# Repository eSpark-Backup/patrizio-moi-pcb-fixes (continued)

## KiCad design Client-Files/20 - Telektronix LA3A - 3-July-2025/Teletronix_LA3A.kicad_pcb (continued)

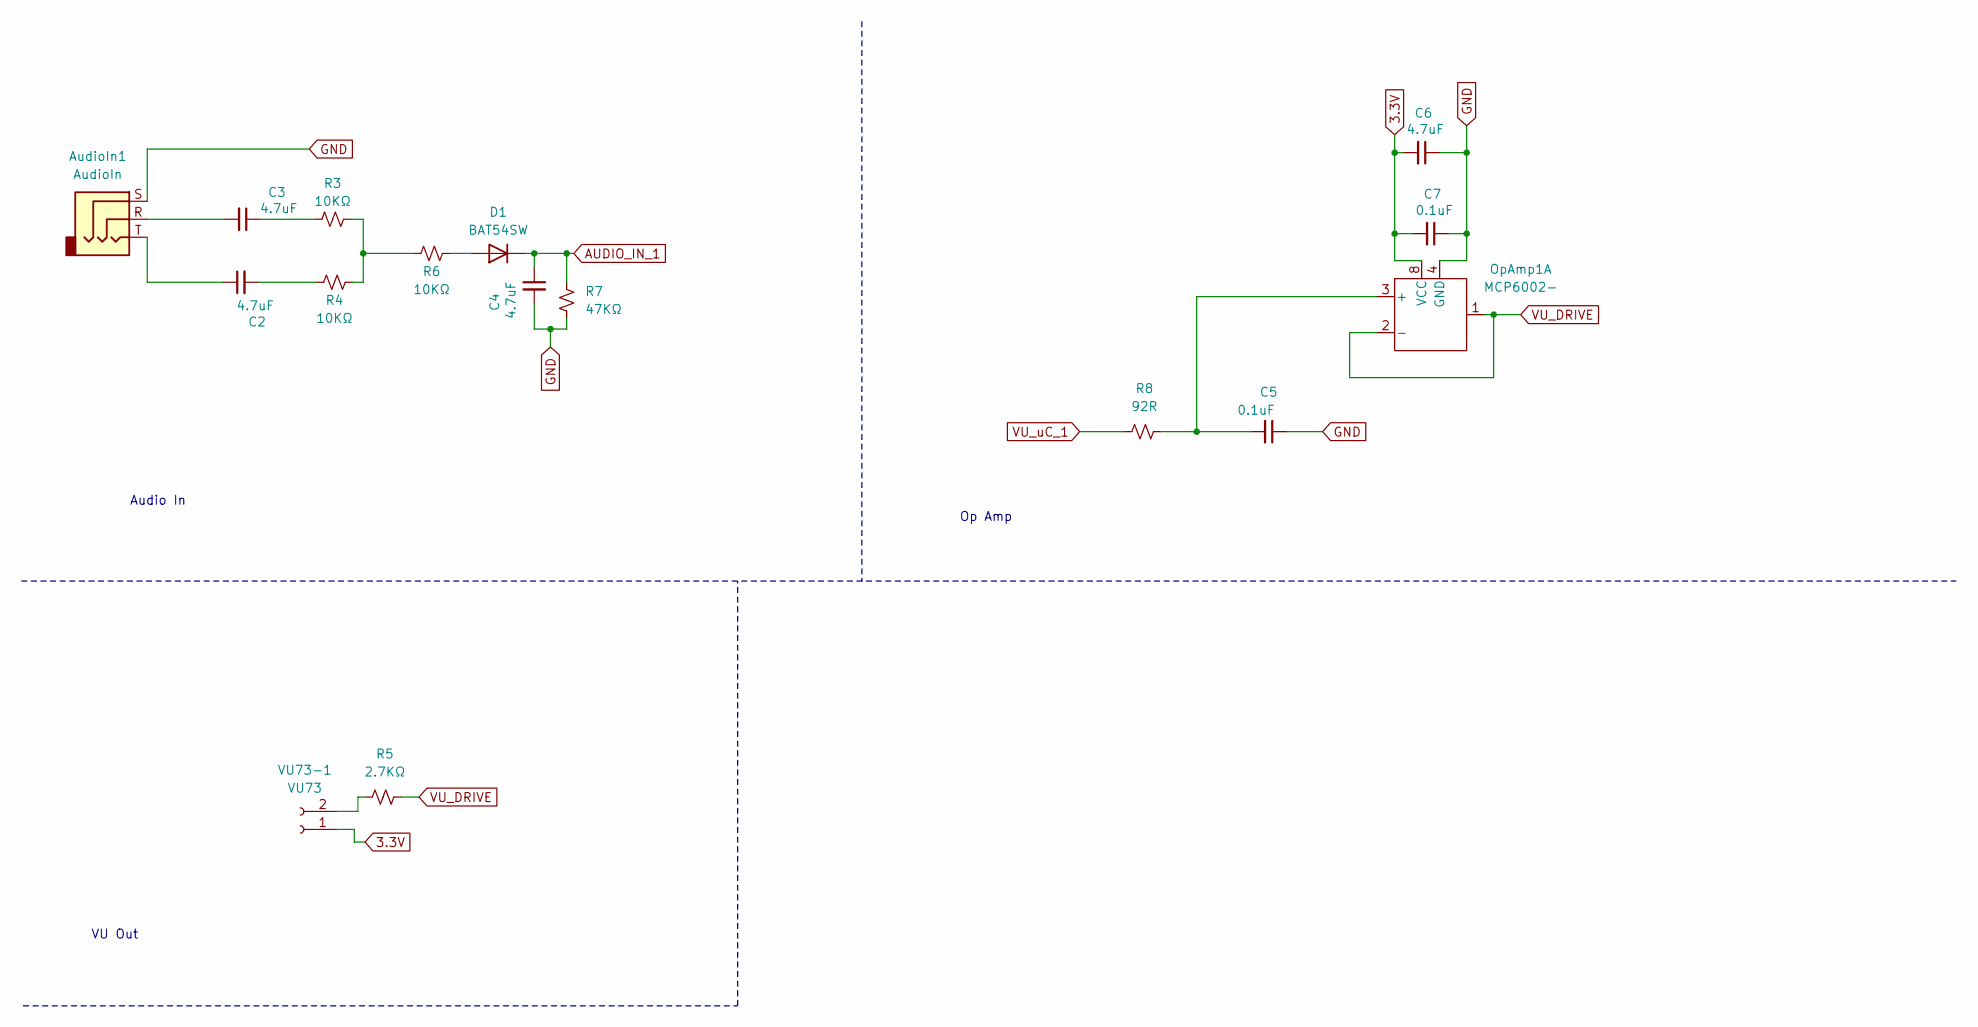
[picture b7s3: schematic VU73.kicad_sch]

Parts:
AudioIn1: AudioIn; Jack_3.5mm_PJ320D_Horizontal; LCSC Part Number C22459515
C2, C3, C4, C6: 4.7uF; C_0402_1005Metric; LCSC Part Number C23733
C5: 0.1uF; C_0402_1005Metric
C7: 0.1uF; C_0402_1005Metric; LCSC Part Number C1525
D1: BAT54SW; D_SOD-323; LCSC Part Number C27636114
OpAmp1: MCP6002-; SOIC-8_3.9x4.9mm_P1.27mm; LCSC Part Number C7377
R3, R4, R6: 10KΩ; R_0402_1005Metric; LCSC Part Number C25744
R5: 2.7KΩ; R_0603_1608Metric; LCSC Part Number C13167
R7: 47KΩ; R_0402_1005Metric; LCSC Part Number C25792
R8: 92R; R_0402_1005Metric
VU73-1: VU73; PinSocket_1x02_P2.54mm_Vertical

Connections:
3.3V: C6.2, C7.2, OpAmp1.8 (VCC), VU73-1.1; also elsewhere on the board
AUDIO_IN_1: C4.1, D1.1 (K), R7.2; also elsewhere on the board
GND: AudioIn1.S, C4.2, C5.1, C6.1, C7.1, OpAmp1.4 (GND), R7.1; also elsewhere on the board
unnamed: AudioIn1.R, C3.2
unnamed: AudioIn1.T, C2.1
unnamed: C2.2, R4.2
unnamed: C3.1, R3.2
unnamed: D1.2 (A), R6.1
unnamed: C5.2, OpAmp1.3 (+), R8.1
unnamed: R3.1, R4.1, R6.2
unnamed: R5.2, VU73-1.2
VU_DRIVE: OpAmp1.1, OpAmp1.2 (-), R5.1
VU_uC_1: R8.2; also elsewhere on the board

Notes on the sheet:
VU Out
Op Amp
Audio In

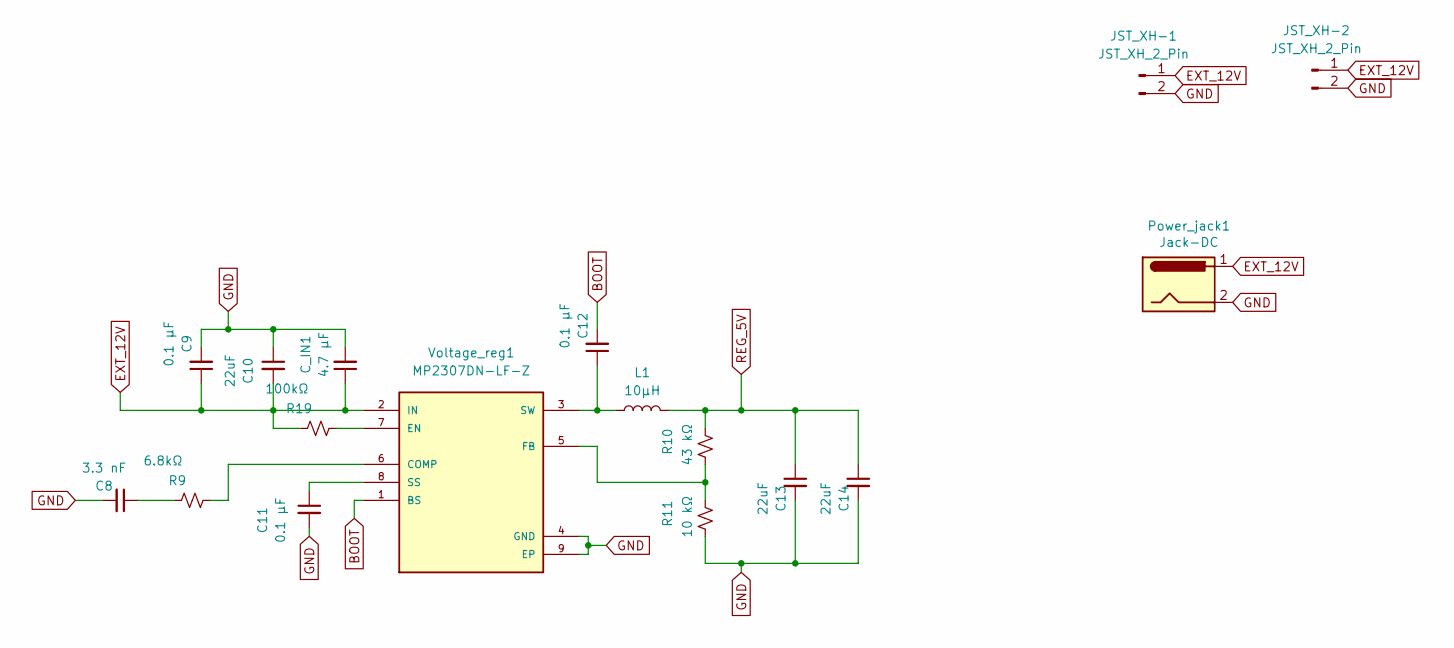
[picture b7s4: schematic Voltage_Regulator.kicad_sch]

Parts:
C8: 3.3 nF; C_0603_1608Metric; LCSC Part Number C1613
C9, C11, C12: 0.1 µF; C_0402_1005Metric; LCSC Part Number C1525
C10, C13, C14: 22uF; C_0603_1608Metric; LCSC Part Number C59461
C_IN1: 4.7 µF; C_0402_1005Metric; LCSC Part Number C23733
JST_XH-1, JST_XH-2: JST_XH_2_Pin; JST_XH_B2B-XH-A_1x02_P2.50mm_Vertical
L1: 10µH; L_Bourns-SRN8040_8x8.15mm; LCSC Part Number C37429
Power_jack1: Jack-DC; BarrelJack_Horizontal
R9: 6.8kΩ; R_0603_1608Metric; LCSC Part Number C23212
R10: 43 kΩ; R_0402_1005Metric; LCSC Part Number C2906943
R11: 10 kΩ; R_0402_1005Metric; LCSC Part Number C25744
R19: 100kΩ; R_0603_1608Metric
Voltage_reg1: MP2307DN-LF-Z; SOIC-8-1EP_3.9x4.9mm_P1.27mm_EP2.29x3mm_ThermalVias; PARTREV 1.9; LCSC Part Number C2928813

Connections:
BOOT: C12.2, Voltage_reg1.1 (BS)
EXT_12V: C9.1, C10.2, C_IN1.1, JST_XH-1.1, JST_XH-2.1, Power_jack1.1, R19.1, Voltage_reg1.2 (IN)
GND: C8.2, C9.2, C10.1, C11.2, C13.2, C14.2, C_IN1.2, JST_XH-1.2, JST_XH-2.2, Power_jack1.2, R11.2, Voltage_reg1.4 (GND), Voltage_reg1.9 (EP); also elsewhere on the board
unnamed: C8.1, R9.1
unnamed: R9.2, Voltage_reg1.6 (COMP)
unnamed: R19.2, Voltage_reg1.7 (EN)
unnamed: R10.2, R11.1, Voltage_reg1.5 (FB)
unnamed: C11.1, Voltage_reg1.8 (SS)
unnamed: C12.1, L1.1, Voltage_reg1.3 (SW)
REG_5V: C13.1, C14.1, L1.2, R10.1; also elsewhere on the board

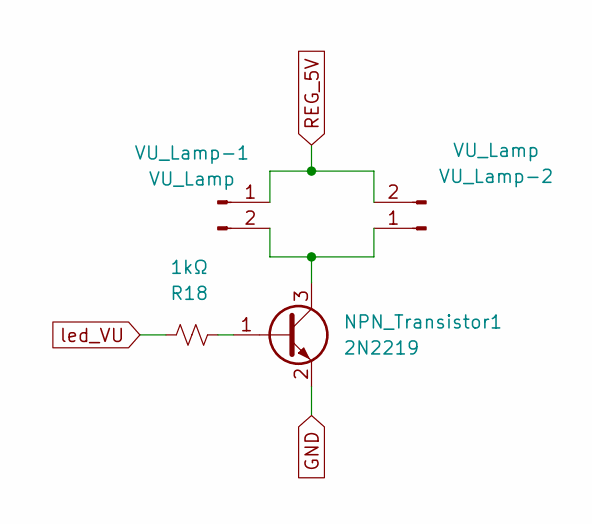
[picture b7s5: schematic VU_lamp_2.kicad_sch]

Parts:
NPN_Transistor1: 2N2219; SOT-23; LCSC Part Number C2150
R18: 1kΩ; R_0402_1005Metric; Manufacturer_Part_Number 0402WGF3300TCE; LCSC Part Number C11702
VU_Lamp-1, VU_Lamp-2: VU_Lamp; PinSocket_1x02_P2.54mm_Vertical

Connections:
GND: NPN_Transistor1.2 (E); also elsewhere on the board
unnamed: NPN_Transistor1.1 (B), R18.1
unnamed: NPN_Transistor1.3 (C), VU_Lamp-1.2, VU_Lamp-2.1
REG_5V: VU_Lamp-1.1, VU_Lamp-2.2; also elsewhere on the board
led_VU: R18.2; also elsewhere on the board

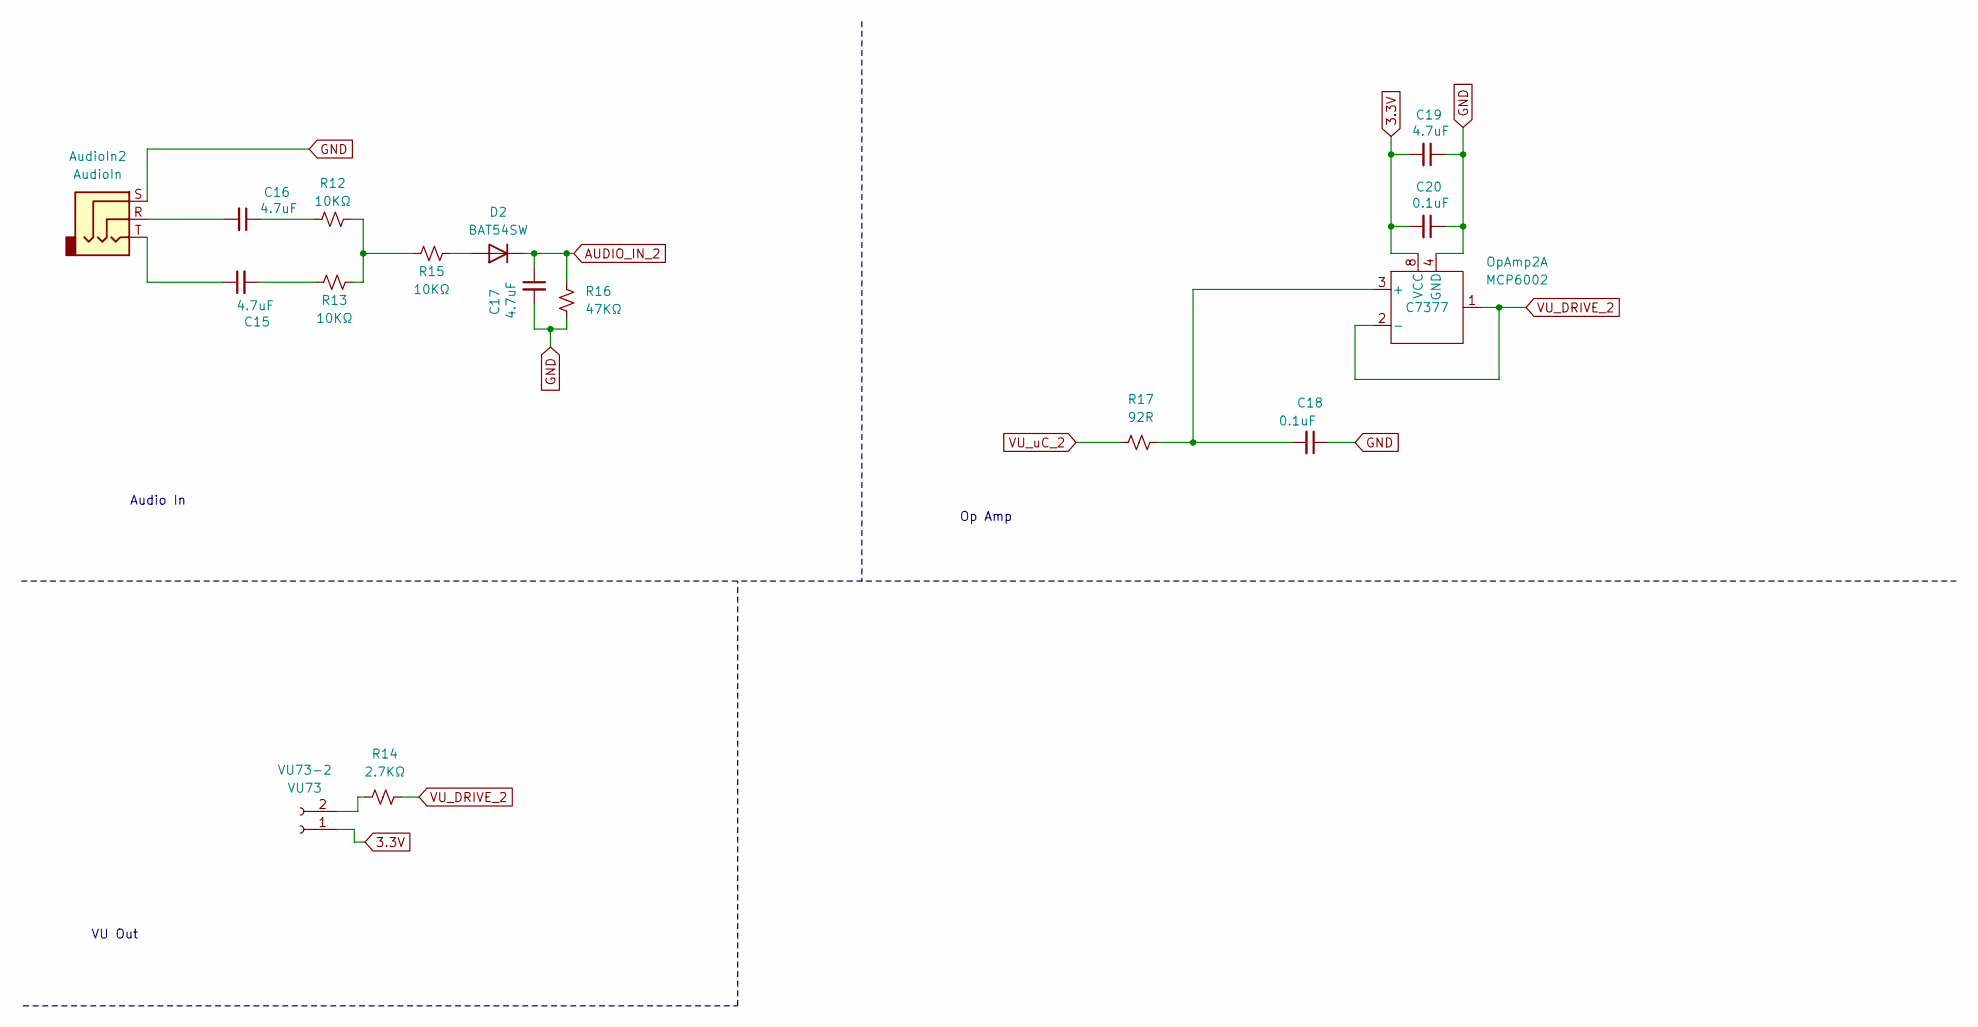
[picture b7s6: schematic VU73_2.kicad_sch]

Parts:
AudioIn2: AudioIn; Jack_3.5mm_PJ320D_Horizontal
C15, C16, C17, C19: 4.7uF; C_0402_1005Metric; LCSC Part Number C23733
C18: 0.1uF; C_0402_1005Metric
C20: 0.1uF; C_0402_1005Metric; LCSC Part Number C1525
D2: BAT54SW; D_SOD-323; LCSC Part Number C27636114
OpAmp2: MCP6002; SOIC-8_3.9x4.9mm_P1.27mm; LCSC Part Number C7377
R12, R13, R15: 10KΩ; R_0402_1005Metric; LCSC Part Number C25744
R14: 2.7KΩ; R_0603_1608Metric; LCSC Part Number C13167
R16: 47KΩ; R_0402_1005Metric; LCSC Part Number C25792
R17: 92R; R_0402_1005Metric
VU73-2: VU73; PinSocket_1x02_P2.54mm_Vertical

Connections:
3.3V: C19.2, C20.2, OpAmp2.8 (VCC), VU73-2.1; also elsewhere on the board
AUDIO_IN_2: C17.1, D2.1 (K), R16.2; also elsewhere on the board
GND: AudioIn2.S, C17.2, C18.1, C19.1, C20.1, OpAmp2.4 (GND), R16.1; also elsewhere on the board
unnamed: AudioIn2.R, C16.2
unnamed: AudioIn2.T, C15.1
unnamed: C15.2, R13.2
unnamed: C16.1, R12.2
unnamed: D2.2 (A), R15.1
unnamed: C18.2, OpAmp2.3 (+), R17.1
unnamed: R12.1, R13.1, R15.2
unnamed: R14.2, VU73-2.2
VU_DRIVE_2: OpAmp2.1, OpAmp2.2 (-), R14.1
VU_uC_2: R17.2; also elsewhere on the board

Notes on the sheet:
VU Out
Op Amp
Audio In

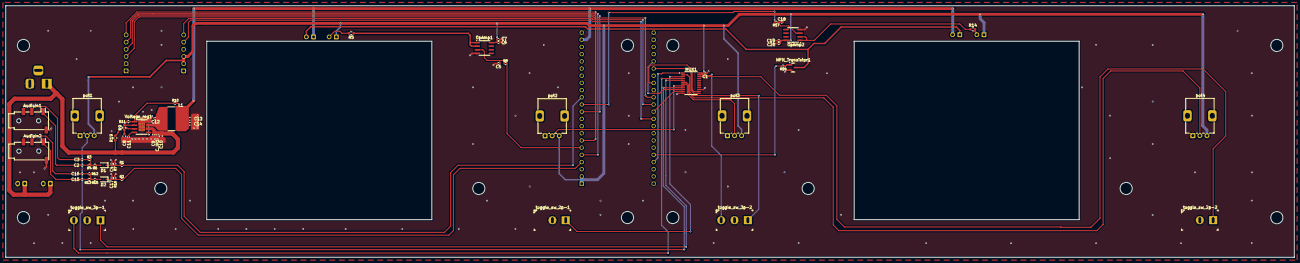
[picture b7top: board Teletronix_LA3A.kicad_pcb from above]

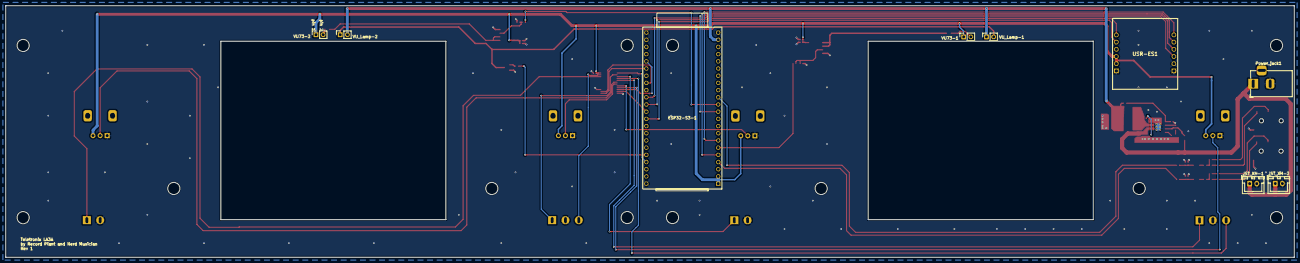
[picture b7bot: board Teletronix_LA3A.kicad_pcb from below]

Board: 2 copper layers, 455.0 x 88.8 mm, 67 parts (9 on the bottom side), 59 nets.

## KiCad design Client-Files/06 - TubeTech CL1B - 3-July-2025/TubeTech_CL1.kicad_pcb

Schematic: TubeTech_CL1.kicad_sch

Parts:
ESP32-S3-1: ESP32-S3-DevKitC; ESP32-S3-DEVKITC-1-N8R2-2
R1: 4.7KΩ; R_0402_1005Metric; LCSC Part Number C25900
USR-ES1: USR-ES1; USRES1; Manufacturer_Part_Number USR-ES1

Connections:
3.3V: ESP32-S3-1.1 (3V3), ESP32-S3-1.2 (3V3), USR-ES1.B2 (3V3_1), USR-ES1.B3 (3V3_2); also elsewhere on the board
AUDIO_IN: R1.1; also elsewhere on the board
CS: ESP32-S3-1.5 (GPIO5/ADC1_CH4), USR-ES1.A5 (CS)
GND: ESP32-S3-1.22 (GND), ESP32-S3-1.23 (GND), ESP32-S3-1.24 (GND), ESP32-S3-1.44 (GND), USR-ES1.A1 (GND_1), USR-ES1.A2 (GND_2), USR-ES1.B1 (GND_3); also elsewhere on the board
INT: ESP32-S3-1.7 (GPIO7/ADC1_CH6), USR-ES1.A6 (INT)
MISO: ESP32-S3-1.33 (GPIO36), USR-ES1.B6 (MISO)
MOSI: ESP32-S3-1.32 (GPIO35), USR-ES1.A3 (MOSI)
unnamed: ESP32-S3-1.13 (GPIO3/ADC1_CH2), R1.2
PWR_BTN: ESP32-S3-1.10 (GPIO17/ADC2_CH6); also elsewhere on the board
PWR_LED: ESP32-S3-1.29 (GPIO48); also elsewhere on the board
REG_5V: ESP32-S3-1.21 (5V); also elsewhere on the board
RST: ESP32-S3-1.35 (GPIO38), USR-ES1.B5 (RST)
S0: ESP32-S3-1.27 (GPIO21); also elsewhere on the board
S1: ESP32-S3-1.34 (GPIO37); also elsewhere on the board
S2: ESP32-S3-1.30 (GPIO45); also elsewhere on the board
S3: ESP32-S3-1.28 (GPIO47); also elsewhere on the board
SCLK: ESP32-S3-1.11 (GPIO18/ADC2_CH7), USR-ES1.A4 (SCLK)
VU_uC_1: ESP32-S3-1.6 (GPIO6/ADC1_CH5); also elsewhere on the board
led_VU: ESP32-S3-1.4 (GPIO4/ADC1_CH3); also elsewhere on the board
sig_1: ESP32-S3-1.41 (GPIO1/ADC1_CH0); also elsewhere on the board

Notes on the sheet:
Ethernet Module
ESP32-S3

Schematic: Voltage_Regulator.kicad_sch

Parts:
C10: 3.3 nF; C_0603_1608Metric; LCSC Part Number C1613
C11, C13, C14: 0.1 µF; C_0402_1005Metric; LCSC Part Number C1525
C12, C15, C16: 22uF; C_0603_1608Metric; LCSC Part Number C59461
C_IN1: 4.7 µF; C_0402_1005Metric; LCSC Part Number C23733
JST_XH-1, JST_XH-2: JST_XH_2_Pin; JST_XH_B2B-XH-A_1x02_P2.50mm_Vertical
L1: 10µH; L_Bourns-SRN8040_8x8.15mm; LCSC Part Number C37429
Power_jack1: Jack-DC; BarrelJack_Horizontal
R14: 6.8kΩ; R_0603_1608Metric; LCSC Part Number C23212
R15: 43 kΩ; R_0402_1005Metric; LCSC Part Number C2906943
R16: 10 kΩ; R_0402_1005Metric; LCSC Part Number C25744
R18: 100kΩ; R_0603_1608Metric
Voltage_reg1: MP2307DN-LF-Z; SOIC-8-1EP_3.9x4.9mm_P1.27mm_EP2.29x3mm_ThermalVias; PARTREV 1.9; LCSC Part Number C2928813

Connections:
BOOT: C14.2, Voltage_reg1.1 (BS)
EXT_12V: C11.1, C12.2, C_IN1.1, JST_XH-1.1, JST_XH-2.1, Power_jack1.1, R18.1, Voltage_reg1.2 (IN)
GND: C10.2, C11.2, C12.1, C13.2, C15.2, C16.2, C_IN1.2, JST_XH-1.2, JST_XH-2.2, Power_jack1.2, R16.2, Voltage_reg1.4 (GND), Voltage_reg1.9 (EP); also elsewhere on the board
unnamed: C10.1, R14.1
unnamed: R14.2, Voltage_reg1.6 (COMP)
unnamed: R18.2, Voltage_reg1.7 (EN)
unnamed: R15.2, R16.1, Voltage_reg1.5 (FB)
unnamed: C13.1, Voltage_reg1.8 (SS)
unnamed: C14.1, L1.1, Voltage_reg1.3 (SW)
REG_5V: C15.1, C16.1, L1.2, R15.1; also elsewhere on the board

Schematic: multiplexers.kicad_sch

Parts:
C7: 0.1uF; C_0402_1005Metric; LCSC Part Number C1525
C8, C9: 2.2uF; C_0402_1005Metric; LCSC Part Number C12530
C17: 2.2uF; C_0402_1005Metric; Manufacturer_Part_Number CL05A225MQ5NSNC; LCSC Part Number C12530
MUX1: CD4067BMT/TR; TSSOP-24_4.4x7.8mm_P0.65mm; LCSC Part Number C7432333
R8, R11: 100Ω; R_0402_1005Metric; LCSC Part Number C25076
R9, R10, R12, R13: 2.2KΩ; R_0402_1005Metric; LCSC Part Number C25879
R19: 100Ω; R_0402_1005Metric; Manufacturer_Part_Number 0402WGF1000TCE; LCSC Part Number C25076
R20: 2.2KΩ; R_0402_1005Metric; Manufacturer_Part_Number 0402WGF2201TCE; LCSC Part Number C25879
RTRY_SW1: SW_Rotary_1x2; SW_Rotary_RS25-2P
SW1, SW2: SW_Rotary_1x3_MP; SW_Rotary_RS25-3P
pot1, pot2, pot3, pot4, pot5, pot6: b10k; Potentiometer_Alps_RK09K_Single_Vertical
tgl_sw_3p-1: SW_SPDT; Toggle_Switch-3-pins

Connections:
3.3V: C7.2, MUX1.24 (VCC), R10.1, R13.1, R20.1, RTRY_SW1.2, SW1.3, SW2.3, pot1.3, pot2.3, pot3.3, pot4.3, pot5.3, pot6.3; also elsewhere on the board
GND: C7.1, C8.1, C9.1, C17.1, MUX1.12 (GND), MUX1.15 (~E), R9.2, R12.2, R20.2, RTRY_SW1.1, SW1.1, SW2.1, pot1.1, pot2.1, pot3.1, pot4.1, pot5.1, pot6.1, tgl_sw_3p-1.2 (B); also elsewhere on the board
I0: MUX1.9 (I0), pot1.2
I1: MUX1.8 (I1), pot2.2
I2: MUX1.7 (I2), pot3.2
I3: MUX1.6 (I3), pot4.2
I4: MUX1.5 (I4), pot5.2
I5: MUX1.4 (I5), pot6.2
I6: MUX1.3 (I6), R8.1
I7: MUX1.2 (I7), R11.1
I8: MUX1.23 (I8), tgl_sw_3p-1.1 (A)
I9: MUX1.22 (I9), tgl_sw_3p-1.3 (C)
unnamed: C8.2, R8.2, SW1.C
unnamed: C9.2, R11.2, SW2.C
unnamed: C17.2, R19.2, RTRY_SW1.C
unnamed: R9.1, R10.2, SW1.2
unnamed: R12.1, R13.2, SW2.2
PWR_BTN: R19.1; also elsewhere on the board
S0: MUX1.10 (S0); also elsewhere on the board
S1: MUX1.11 (S1); also elsewhere on the board
S2: MUX1.14 (S2); also elsewhere on the board
S3: MUX1.13 (S3); also elsewhere on the board
sig_1: MUX1.1 (COM); also elsewhere on the board

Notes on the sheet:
4067

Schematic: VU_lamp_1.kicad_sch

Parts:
NPN_Transistor1, NPN_Transistor2: 2N2219; SOT-23; LCSC Part Number C2150
PWR1: LED; PinSocket_1x02_P2.54mm_Vertical
R17, R21: 1kΩ; R_0402_1005Metric; Manufacturer_Part_Number 0402WGF3300TCE; LCSC Part Number C11702
VU_Lamp-1: VU_Lamp; PinSocket_1x02_P2.54mm_Vertical

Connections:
GND: NPN_Transistor1.2 (E), NPN_Transistor2.2 (E); also elsewhere on the board
unnamed: NPN_Transistor1.1 (B), R17.1
unnamed: NPN_Transistor1.3 (C), VU_Lamp-1.2
unnamed: NPN_Transistor2.1 (B), R21.1
unnamed: NPN_Transistor2.3 (C), PWR1.1 (K)
PWR_LED: R21.2; also elsewhere on the board
REG_5V: PWR1.2 (A), VU_Lamp-1.1; also elsewhere on the board
led_VU: R17.2; also elsewhere on the board

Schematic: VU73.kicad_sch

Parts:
AudioIn1: AudioIn; Jack_3.5mm_PJ320D_Horizontal; LCSC Part Number C22459515
C1, C2, C3, C5: 4.7uF; C_0402_1005Metric; LCSC Part Number C23733
C4: 0.1uF; C_0402_1005Metric
C6: 0.1uF; C_0402_1005Metric; LCSC Part Number C1525
D1: BAT54SW; D_SOD-323; LCSC Part Number C27636114
OpAmp2: MCP6002-; SOIC-8_3.9x4.9mm_P1.27mm; LCSC Part Number C7377
R2, R3, R5: 10KΩ; R_0402_1005Metric; LCSC Part Number C25744
R4: 2.7KΩ; R_0603_1608Metric; LCSC Part Number C13167
R6: 47KΩ; R_0402_1005Metric; LCSC Part Number C25792
R7: 92R; R_0402_1005Metric
VU73-1: VU73; PinSocket_1x02_P2.54mm_Vertical

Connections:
3.3V: C5.2, C6.2, OpAmp2.8 (VCC), VU73-1.1; also elsewhere on the board
AUDIO_IN: C3.1, D1.1 (K), R6.2; also elsewhere on the board
GND: AudioIn1.S, C3.2, C4.1, C5.1, C6.1, OpAmp2.4 (GND), R6.1; also elsewhere on the board
unnamed: AudioIn1.R, C2.2
unnamed: AudioIn1.T, C1.1
unnamed: C1.2, R3.2
unnamed: C2.1, R2.2
unnamed: D1.2 (A), R5.1
unnamed: C4.2, OpAmp2.3 (+), R7.1
unnamed: R2.1, R3.1, R5.2
unnamed: R4.2, VU73-1.2
VU_DRIVE: OpAmp2.1, OpAmp2.2 (-), R4.1
VU_uC_1: R7.2; also elsewhere on the board

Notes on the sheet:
VU Out
Op Amp
Audio In

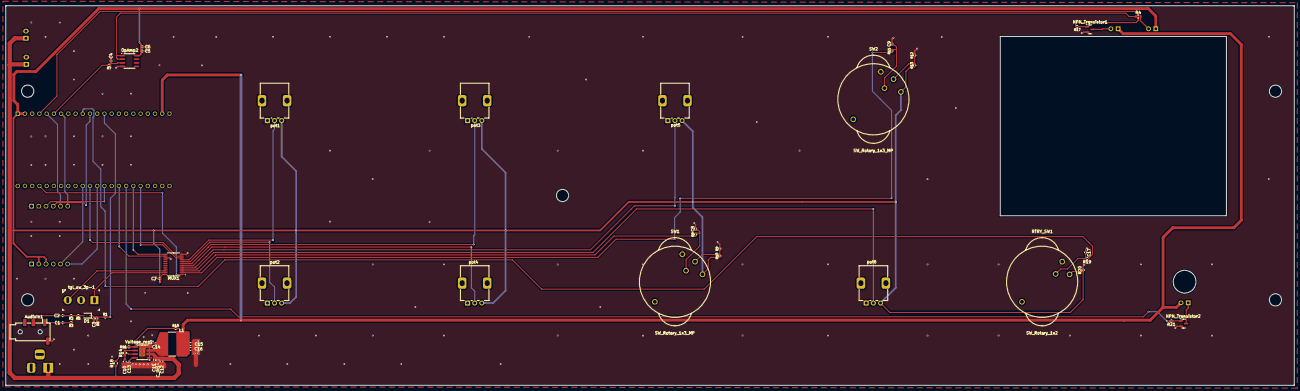
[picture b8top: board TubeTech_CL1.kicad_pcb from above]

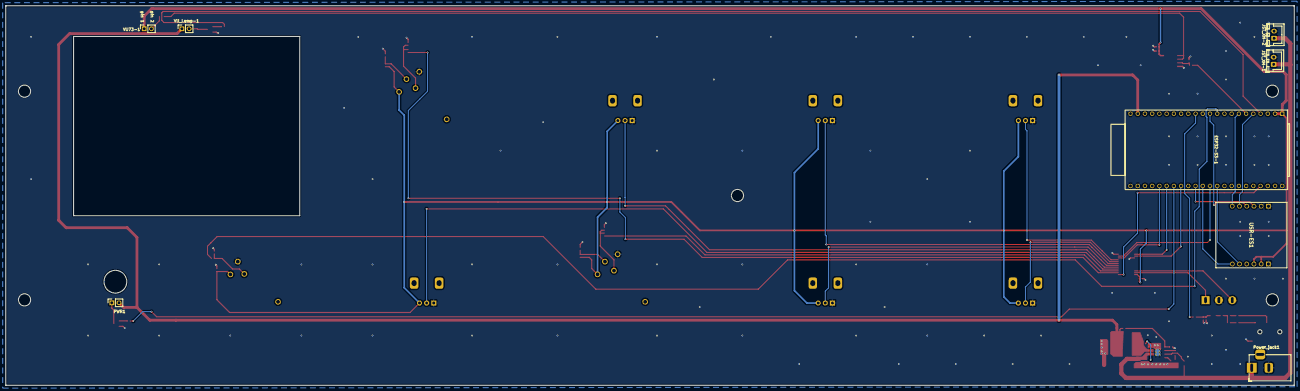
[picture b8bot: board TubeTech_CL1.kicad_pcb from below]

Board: 2 copper layers, 452.9 x 133.4 mm, 65 parts (8 on the bottom side), 56 nets.

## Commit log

2025-07-31 Client Files pushed
2025-08-01 MAC files removed
2025-08-01 #1 Placement in progress
2025-08-04 Design_files folder added
2025-08-04 #1 Routing in progress
2025-08-05 #1 Completed
2025-08-06 #3 Completed Deliverables generated
2025-08-06 #4 in progress
2025-08-07 #4 Completed
